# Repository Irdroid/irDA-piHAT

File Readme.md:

# irDA piHAT Transceiver for Raspberry Pi

The IrDA piHAT is a IrDA SIR transceiver HAT for raspberry Pi. It will allow you to experiment and develop solutions that require IrDA SIR serial communication from 9600 to 115200 baud rates. The IrDA piHAT comes pre-configured for 9600 bps serial SIR communication with the target IR device.

- Complete solution for IrDA communication on Raspberry Pi
- Supports with IrDA® Physical Layer Specification (version 1.3)
- High quality infrared transceiver
- Up to *5 meters IrDA SIR communication
- Supports Baud rates from 9600 – 115200 bps
- No drivers are required

### Version
1.0
### Grab a sample

You can grab a sample board from https://irdroid.eu/product/irda-pihat/

### Todos

 - n/a
 
License
----
GPL 2.0

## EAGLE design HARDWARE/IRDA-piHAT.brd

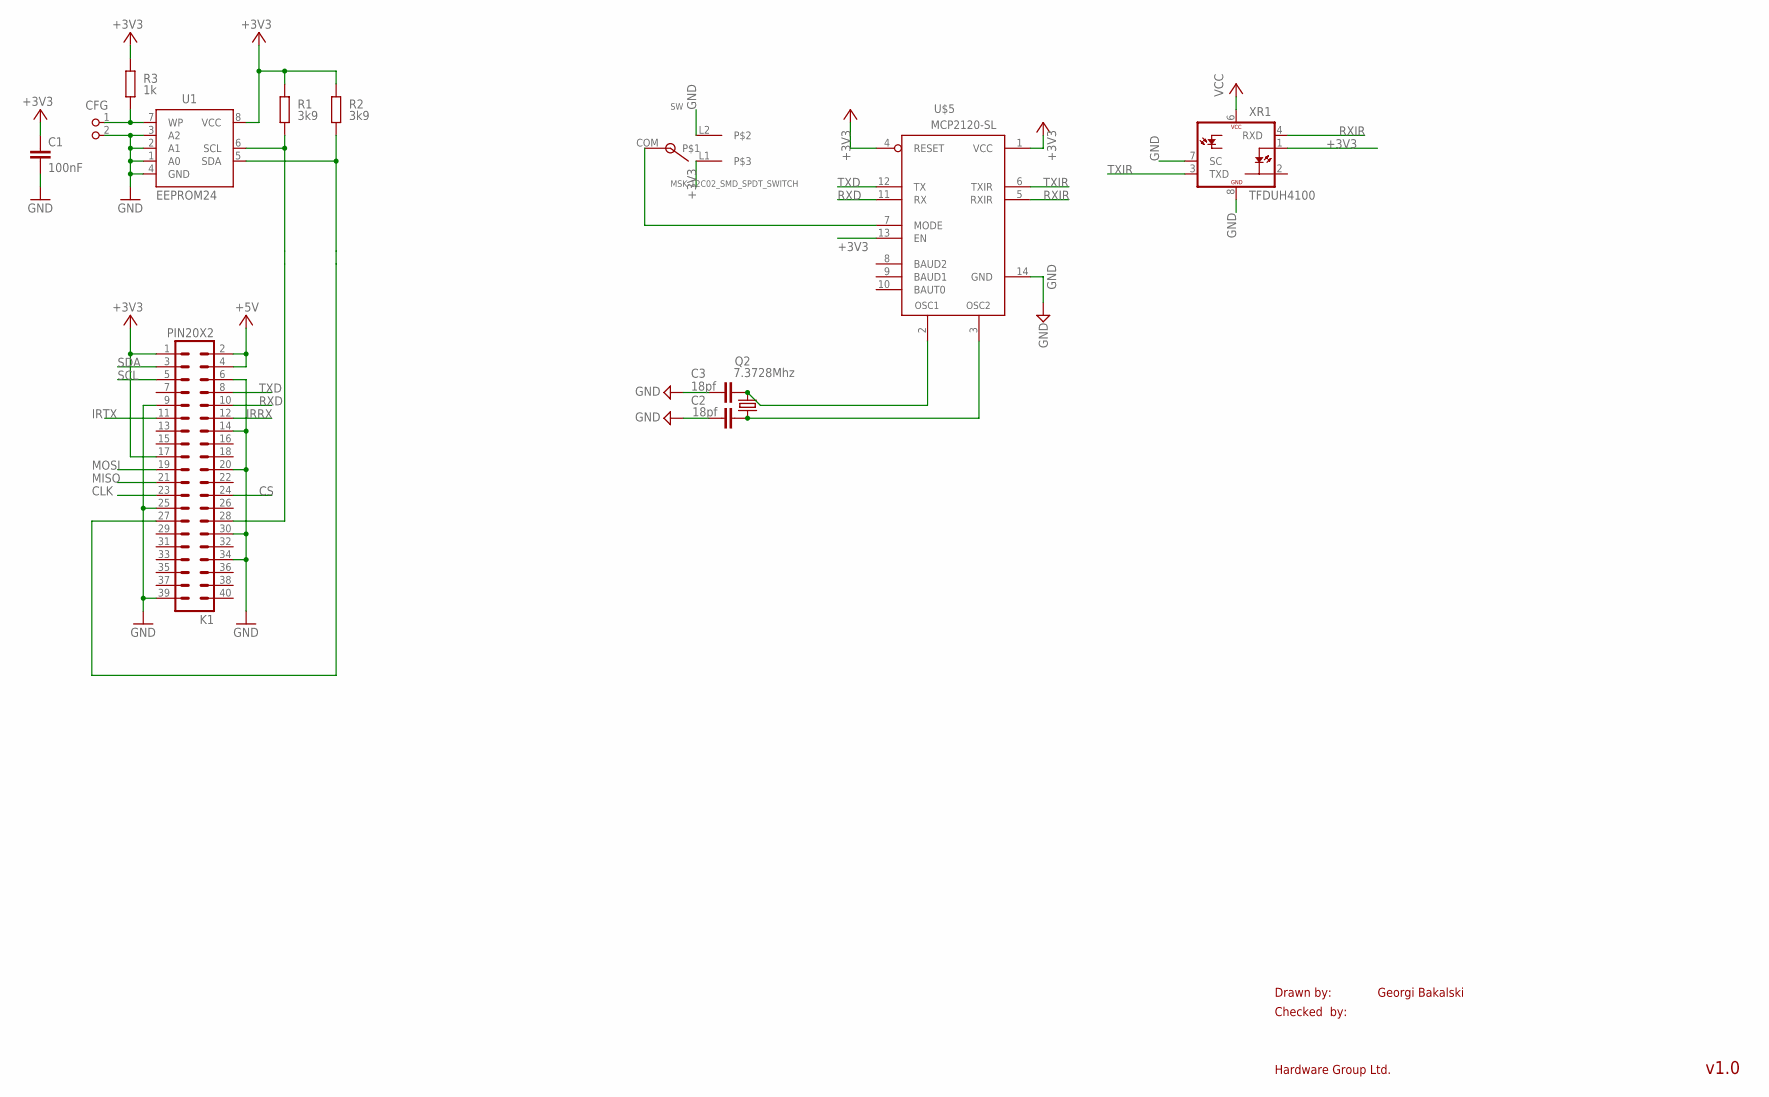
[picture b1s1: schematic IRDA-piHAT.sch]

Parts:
C1: 100nF; C0805K
C2, C3: 18pf; C603
CFG: PIN2_100; PIN_W_2
K1: PIN20X2; PIN_20X2
Q2: 7.3728Mhz; HC49UP
R1, R2: 3k9; M0805; TOLERANCE 5%
R3: 1k; M0805; TOLERANCE 5%
SW: MSK-12C02_SMD_SPDT_SWITCH; MSK-12C02
U1: EEPROM24; SOIC8
U$5: MCP2120-SL; SO-14
XR1: TFDUH4100; TFDU4-HOR

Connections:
+3V3: C1.1, K1.1, K1.17, R1.2, R2.2, R3.2, SW.L1, U1.8 (VCC), U$5.1 (VCC), U$5.4 (RESET), U$5.13 (EN), XR1.1 (IRED-A), XR1.6 (VCC)
+5V: K1.2, K1.4
CLK: K1.23
CS: K1.24
GND: C1.2, C2.2, C3.2, CFG.2, K1.6, K1.9, K1.14, K1.20, K1.25, K1.30, K1.34, K1.39, SW.L2, U1.1 (A0), U1.2 (A1), U1.3 (A2), U1.4 (GND), U$5.14 (GND), XR1.7 (SC), XR1.8 (GND)
IRRX: K1.12
IRTX: K1.11
MISO: K1.21
MOSI: K1.19
unnamed: CFG.1, R3.1, U1.7 (WP)
unnamed: C3.1, Q2.2, U$5.2 (OSC1)
unnamed: C2.1, Q2.1, U$5.3 (OSC2)
unnamed: SW.COM, U$5.7 (MODE)
unnamed: K1.28, R1.1, U1.6 (SCL)
unnamed: K1.27, R2.1, U1.5 (SDA)
RXD: K1.10, U$5.11 (RX)
RXIR: U$5.5 (RXIR), XR1.4 (RXD)
SCL: K1.5
SDA: K1.3
TXD: K1.8, U$5.12 (TX)
TXIR: U$5.6 (TXIR), XR1.3 (TXD)

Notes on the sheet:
Drawn by:
Checked by:
Hardware Group Ltd.
Georgi Bakalski
v1.0

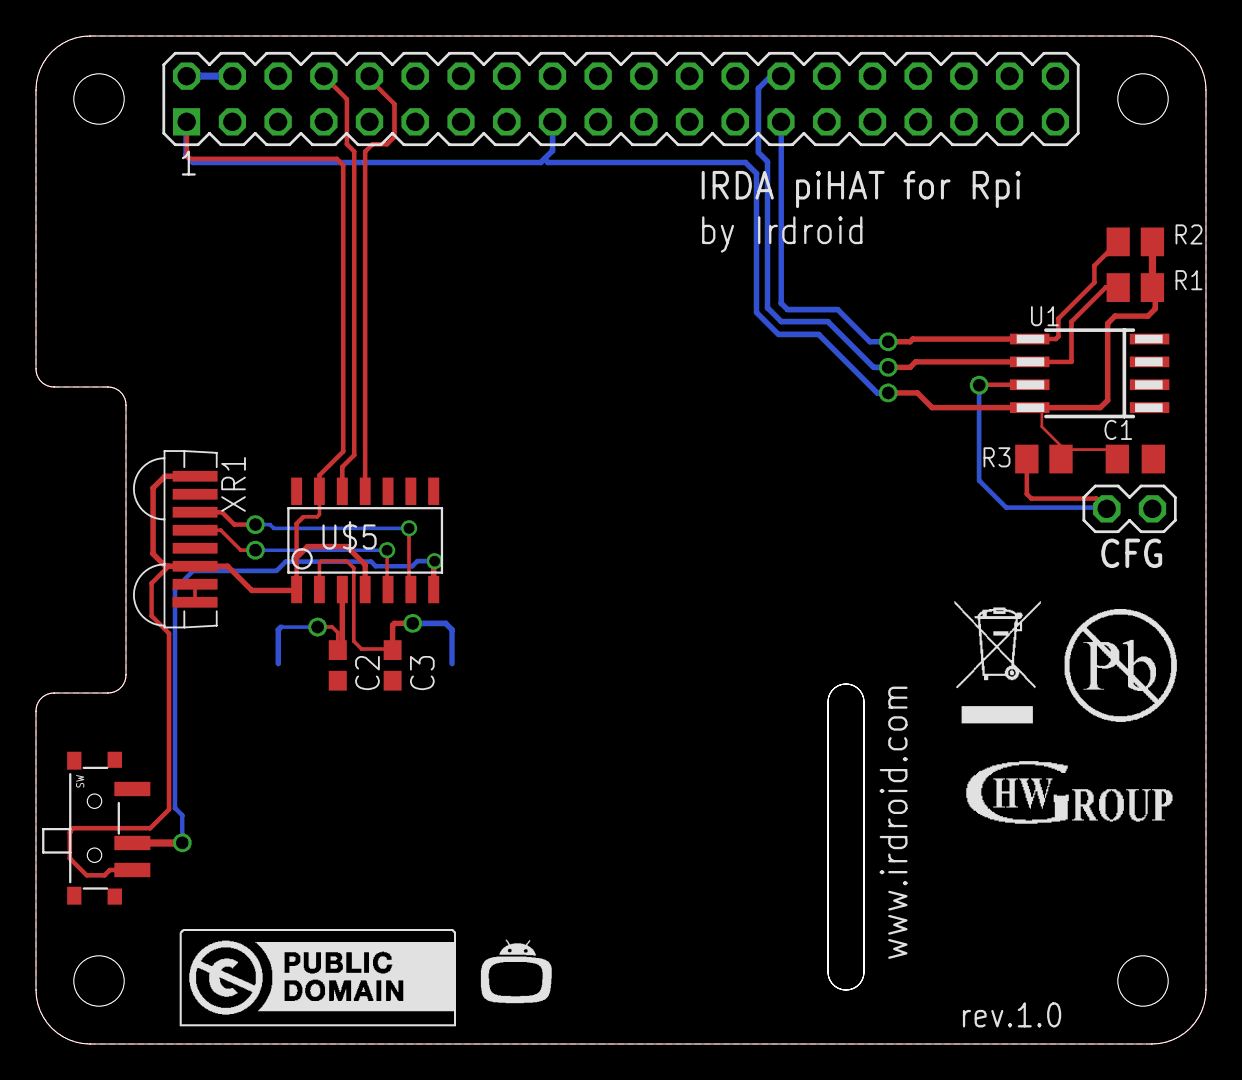
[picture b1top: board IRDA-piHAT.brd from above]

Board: 2 copper layers, 65.0 x 56.0 mm, 17 parts (1 on the bottom side), 13 nets.

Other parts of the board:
U$1: LOGO_CC-0
U$2: IRDROIDLOGO
U$3: TRASH
U$4: HWGROUP

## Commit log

2019-03-29 Initial Commit
    Initial Commit
2019-03-29 updated Readme.md
    updated readme.md
2019-03-29 updated md
    md
2019-03-29 another readme.md update
    another readme.md update
